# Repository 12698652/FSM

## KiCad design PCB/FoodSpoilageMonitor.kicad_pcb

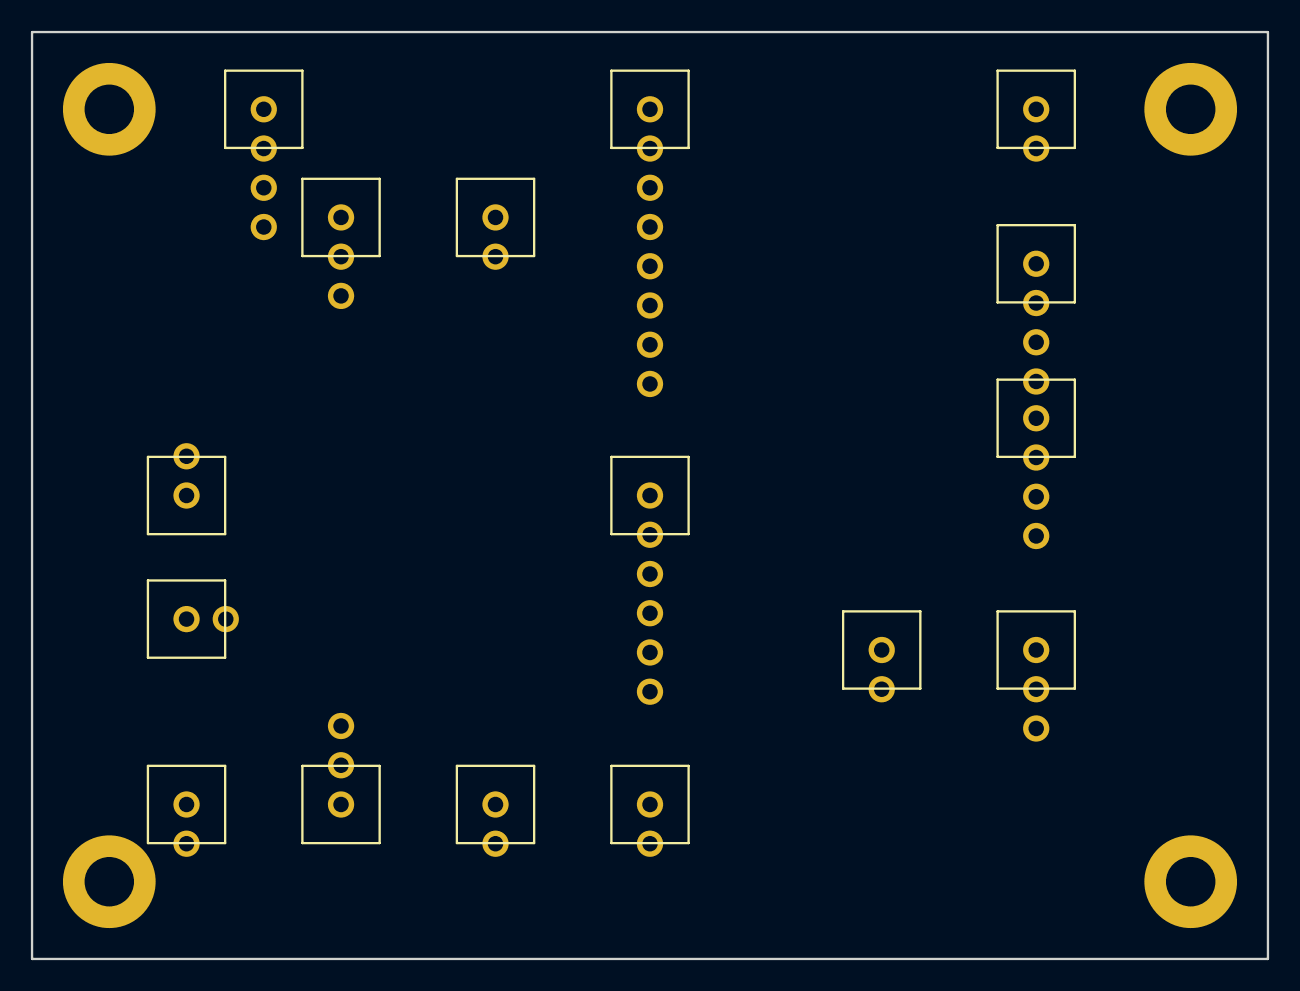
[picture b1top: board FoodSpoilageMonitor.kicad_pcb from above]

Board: 2 copper layers, 80.0 x 60.0 mm, 20 parts (0 on the bottom side), 9 nets, no tracks yet.

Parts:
C1: 10uF; CP_Radial_D5.0mm_P2.50mm
C2: 100nF; C_0805_2012Metric
D1: LED Red; LED_D5.0mm
F1: PTC 1.1A; Fuse_BelFuse_0ZCF0005FF_C6.3x5.1
J1: 5V/3A; TerminalBlock_bornier-2_P5.08mm
M1: FAN 5V; PinHeader_1x02_P2.54mm_Vertical
R1: 150R; R_Axial_DIN0207_L6.3mm_D2.5mm_P10.16mm_Horizontal
REF: M3; MountingHole_3.2mm_M3
REF#2, REF#3, REF#4: M3; MountingHole_3.2mm_M3
SW1: 总开关; SW_CuK_OS102011MA1QN1_SPDT_Angled
SW2: 风扇开关; SW_CuK_OS102011MA1QN1_SPDT_Angled
TB1: TB1; TerminalBlock_bornier-4_P5.08mm
TB2: TB2; TerminalBlock_bornier-8_P5.08mm
TB3: TB3; TerminalBlock_bornier-2_P5.08mm
U1: ESP32; PinHeader_1x06_P2.54mm_Vertical
U2: BME680; PinHeader_1x04_P2.54mm_Vertical
U3: SGP30; PinHeader_1x04_P2.54mm_Vertical
U4: MQ-137; PinHeader_1x03_P2.54mm_Vertical

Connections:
+3V3: TB1.4, TB2.5, U1.3, U2.1, U3.1
+5V: C1.1, F1.2, J1.1, R1.1, SW1.1, SW2.1, TB1.1, TB1.3, TB2.6, U1.1, U4.1
FAN_OUT: M1.1, SW2.2, TB3.1
GND: C1.2, C2.2, D1.1, J1.2, M1.2, TB1.2, TB2.4, TB2.7, TB3.2, U1.2, U2.2, U3.2, U4.2
LED_A: D1.2, R1.2
NH3_AO: C2.1, TB2.3, U1.6, U4.3
Net-SW1F1: F1.1, SW1.2
SCL: TB2.2, U1.5, U2.4, U3.4
SDA: TB2.1, U1.4, U2.3, U3.3

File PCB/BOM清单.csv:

序号,位号,元件名称,规格/值,封装,数量,嘉立创物料编号(参考),备注
1,J1,USB端子,5V/3A输入,KF128-2P-5.08,1,-,电源输入
2,SW1,SW2,拨动开关,SS-12F15 1P2T,SPDT,2,C319690,总开关+风扇开关
3,F1,自恢复保险丝,PPTC 1.1A,0ZCG0110FF2C,1,C155325,5V过流保护
4,C1,电解电容,10uF/25V,5×7mm D5.0 P2.5,1,C46584,5V滤波
5,C2,陶瓷电容,100nF/50V X7R,0805,1,C49678,ADC滤波
6,U1,ESP32开发板,ESP32-WROOM-32,NodeMCU-32S,1,C828287,主控(沿用已有)
7,U2,BME680模块,温湿度+气压+VOC,4P 2.54mm排针,1,C83691,I²C 0x76
8,U3,SGP30模块,TVOC+eCO2,4P 2.54mm排针,1,C83692,I²C 0x58
9,U4,MQ-137模块,氨气传感器,3P 2.54mm排针,1,C83693,模拟输出
10,M1,直流风扇,5V/0.15A 40×40mm,2P 2.54mm排针,1,C83694,空气循环
11,D1,LED,红色5mm,D5.0mm,1,C84263,电源指示
12,R1,电阻,150Ω 1/4W,THT D0207,1,C17415,LED限流
13,TB1,端子排,4P 5.08mm,KF128-4P,1,C83695,电源分配
14,TB2,端子排,8P 5.08mm,KF128-8P,1,C83696,信号
15,TB3,端子排,2P 5.08mm,KF128-2P,1,C83697,风扇
16,-,M3螺丝,M3×6mm,-,4,-,安装孔
